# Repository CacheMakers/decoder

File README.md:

# decoder
arduino-based decoder ring

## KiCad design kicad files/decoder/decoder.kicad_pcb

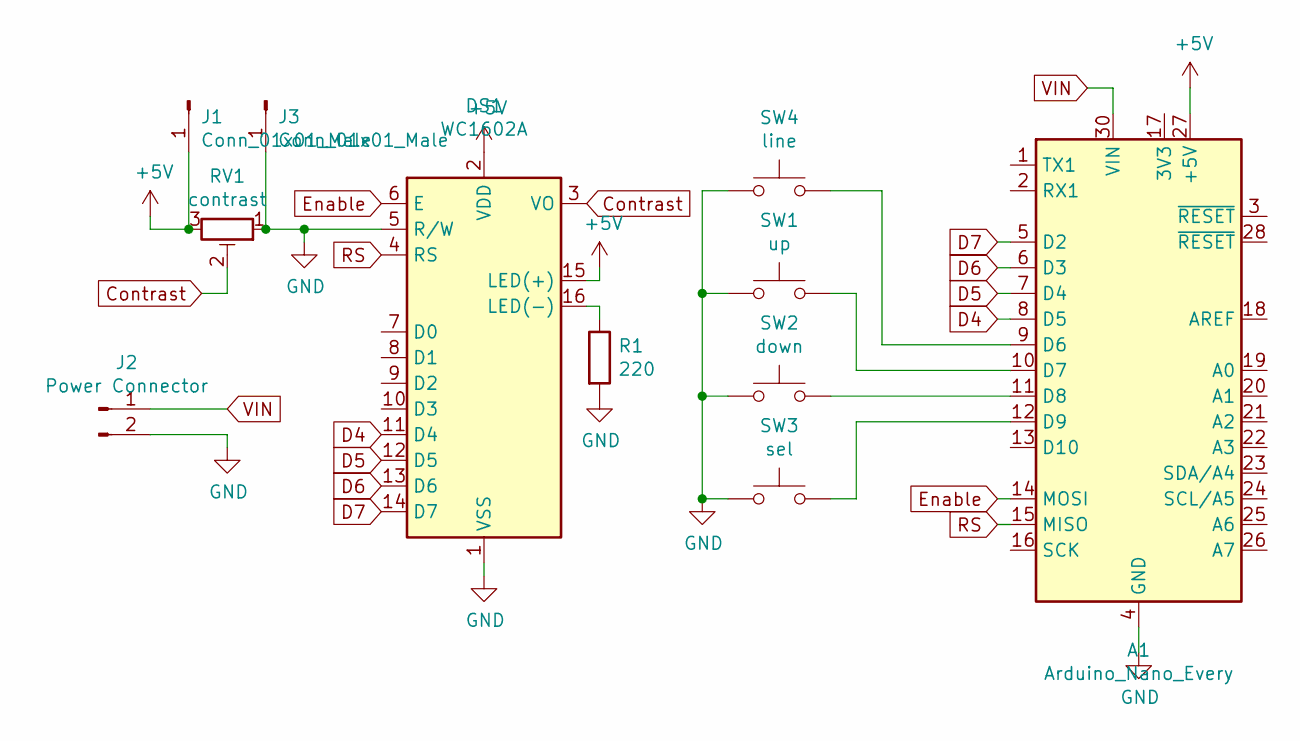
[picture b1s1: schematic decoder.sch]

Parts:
A1: Arduino_Nano_Every; Arduino_Nano
DS1: WC1602A
J1, J3: Conn_01x01_Male; PinHeader_1x01_P2.54mm_Vertical
J2: Power Connector; PinHeader_1x02_P2.54mm_Horizontal
R1: 220; R_Axial_DIN0309_L9.0mm_D3.2mm_P12.70mm_Horizontal
RV1: contrast; Potentiometer_Vishay_T73YP_Vertical
SW1: up; SW_PUSH_6mm
SW2: down; SW_PUSH_6mm
SW3: sel; SW_PUSH_6mm
SW4: line; SW_PUSH_6mm

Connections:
+5V: A1.27 (+5V), DS1.2 (VDD), DS1.15 (LED(+)), J1.1, RV1.3
Contrast: DS1.3 (VO), RV1.2
D4: A1.8 (D5), DS1.11 (D4)
D5: A1.7 (D4), DS1.12 (D5)
D6: A1.6 (D3), DS1.13 (D6)
D7: A1.5 (D2), DS1.14 (D7)
Enable: A1.14 (MOSI), DS1.6 (E)
GND: A1.4 (GND), A1.29 (GND), DS1.1 (VSS), DS1.5 (R/W), J2.2, J3.1, R1.2, RV1.1, SW1.1, SW2.1, SW3.1, SW4.1
unnamed: A1.9 (D6), SW4.2
unnamed: A1.10 (D7), SW1.2
unnamed: A1.11 (D8), SW2.2
unnamed: A1.12 (D9), SW3.2
unnamed: DS1.16 (LED(-)), R1.1
RS: A1.15 (MISO), DS1.4 (RS)
VIN: A1.30 (VIN), J2.1

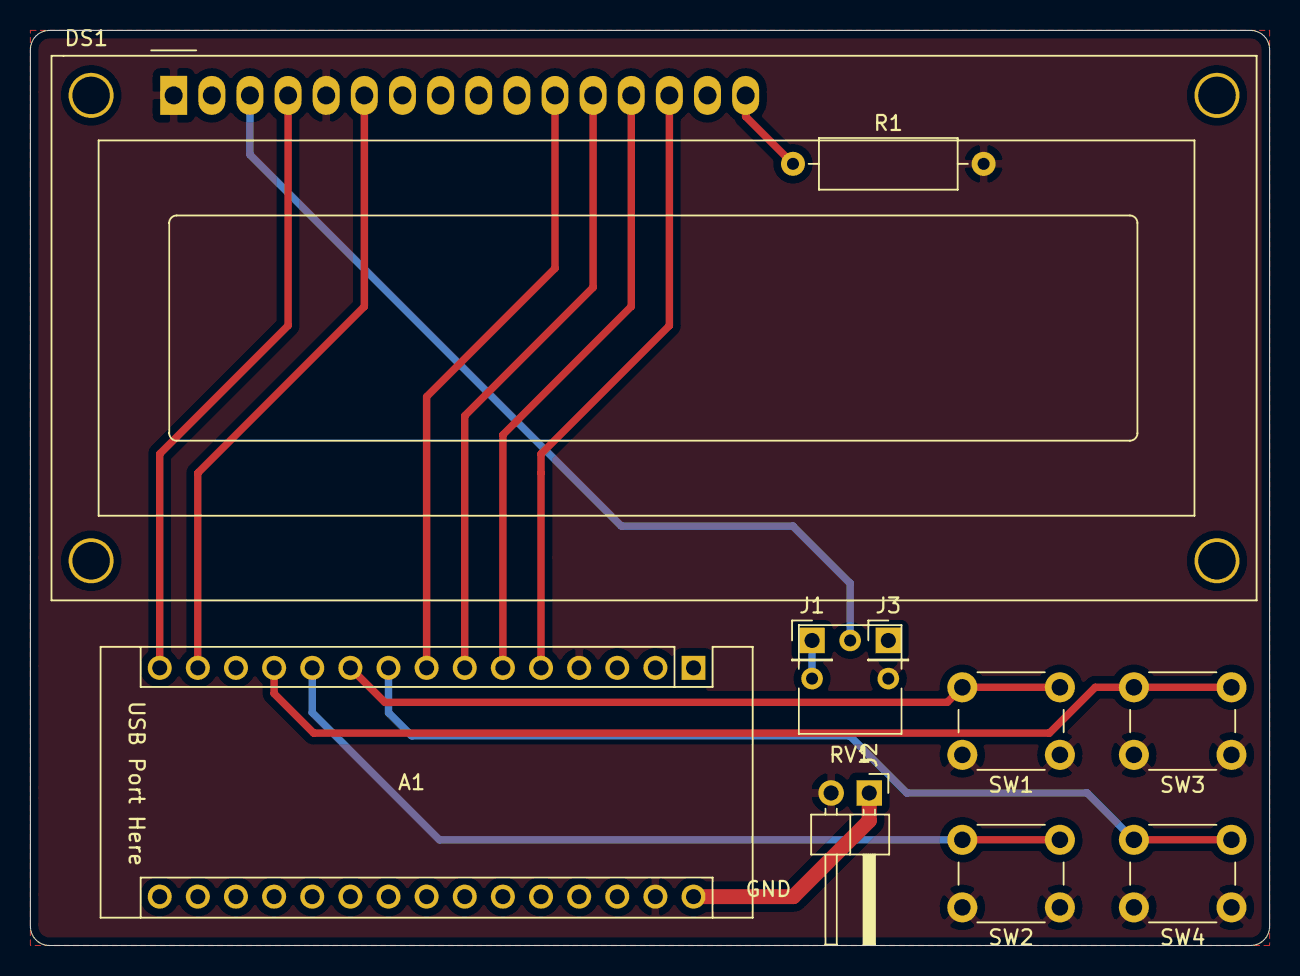
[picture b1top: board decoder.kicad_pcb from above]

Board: 2 copper layers, 82.6 x 61.0 mm, 11 parts (0 on the bottom side), 15 nets.

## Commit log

2021-04-13 added line button
2021-05-21 final changes to PCB, started to clean up code on first gen PCB
2021-05-21 fixed an issue on the first rev of the PCB
2021-05-21 added an example cypher
2021-05-21 added some explanatory comments to cypher.h
2021-06-10 fixed an error in the example decode function
